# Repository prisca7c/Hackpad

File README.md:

# AccentBean
AccentBean is an 8 key macropad with a rotary encoder and an OLED Display. It has a detachable magnetic OLED case, and uses KMK firmware. The purpose of this macropad is to make typing diacritics easier by holding both letter and accent at the same time. 

## Overall Hackpad

## Schematic

## PCB

## Case + Assembly

## Bill of Materials (BOM)
- 1x Seeed XIAO RP2040
- 4x 5x2mm magnets (https://www.aliexpress.com/item/1005009038424067.html?spm=a2g0o.detail.0.0.5b1dKrIMKrIMbR&mp=1&pdp_npi=5%40dis%21CAD%21CAD%205.59%21CAD%205.59%21%21CAD%205.59%21%21%21%402103244b17520167383694920ea1b1%2112000047709478195%21ct%21CA%216390044033%21%211%210)
- 4X M3x12mm SHCS Bolts
- 8x Cherry MX Switches
- 8x DSA Keycaps
- 8x 1N4148 DO-35 Diodes
- 1x EC11 Rotary Encoder
- 1x 0.91" 128x32mm OLED Display
- 1x Case (3 printed parts)

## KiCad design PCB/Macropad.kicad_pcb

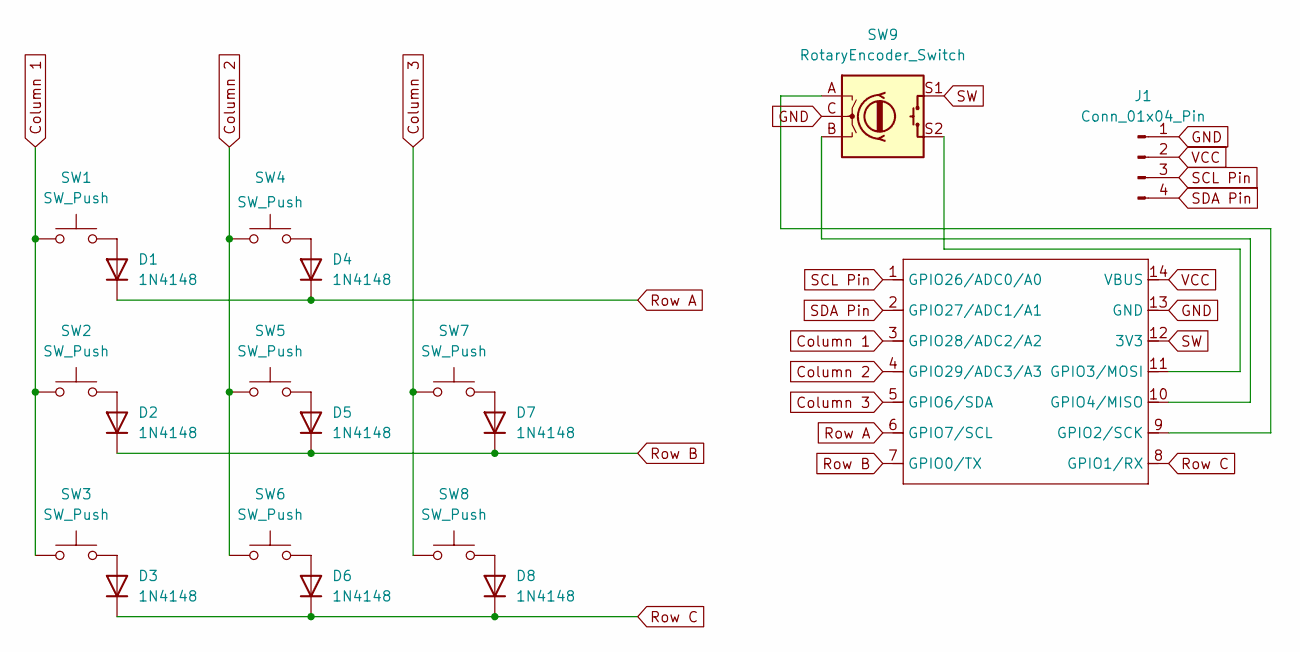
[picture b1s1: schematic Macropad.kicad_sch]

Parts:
D1, D2, D3, D4, D5, D6, D7, D8: 1N4148; D_DO-35_SOD27_P7.62mm_Horizontal
J1: Conn_01x04_Pin; SSD1306-0.91-OLED-4pin-128x32
SW1, SW2, SW3, SW4, SW5, SW6, SW7, SW8: SW_Push; SW_Cherry_MX_1.00u_PCB
SW9: RotaryEncoder_Switch; RotaryEncoder_Alps_EC11E-Switch_Vertical_H20mm
U1: XIAO-RP2040-DIP

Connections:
Column 1: SW1.1, SW2.1, SW3.1, U1.3 (GPIO28/ADC2/A2)
Column 2: SW4.1, SW5.1, SW6.1, U1.4 (GPIO29/ADC3/A3)
Column 3: SW7.1, SW8.1, U1.5 (GPIO6/SDA)
GND: J1.1, SW9.C, U1.13 (GND)
unnamed: D1.2 (A), SW1.2
unnamed: D2.2 (A), SW2.2
unnamed: D3.2 (A), SW3.2
unnamed: D4.2 (A), SW4.2
unnamed: D5.2 (A), SW5.2
unnamed: D6.2 (A), SW6.2
unnamed: D7.2 (A), SW7.2
unnamed: D8.2 (A), SW8.2
unnamed: SW9.A, U1.9 (GPIO2/SCK)
unnamed: SW9.S2, U1.11 (GPIO3/MOSI)
unnamed: SW9.B, U1.10 (GPIO4/MISO)
Row A: D1.1 (K), D4.1 (K), U1.6 (GPIO7/SCL)
Row B: D2.1 (K), D5.1 (K), D7.1 (K), U1.7 (GPIO0/TX)
Row C: D3.1 (K), D6.1 (K), D8.1 (K), U1.8 (GPIO1/RX)
SCL Pin: J1.3, U1.1 (GPIO26/ADC0/A0)
SDA Pin: J1.4, U1.2 (GPIO27/ADC1/A1)
SW: SW9.S1, U1.12 (3V3)
VCC: J1.2, U1.14 (VBUS)

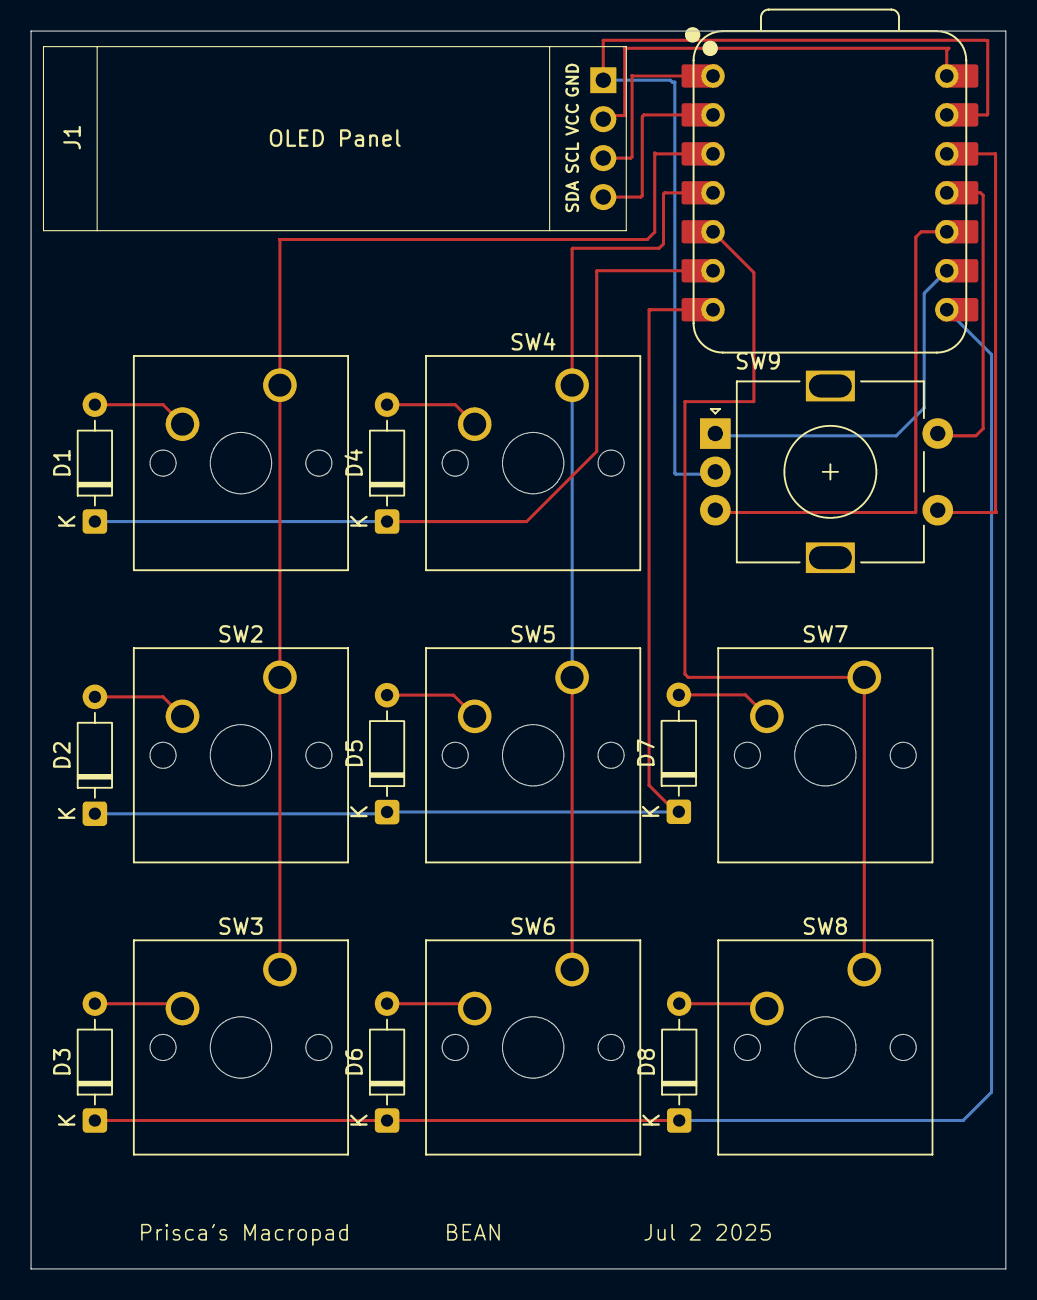
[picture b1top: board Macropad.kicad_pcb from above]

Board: 2 copper layers, 63.6 x 80.7 mm, 19 parts (0 on the bottom side), 22 nets.

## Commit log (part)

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2025-07-02 Create hackpad
2025-07-02 Create pro
2025-07-02 Create kmk
2025-07-02 Create file
